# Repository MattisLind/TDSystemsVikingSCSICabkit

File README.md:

# Adapter board for Viking SCSI cards

This is an adapter board for the TD Systems line of Viking SCSI cards for DEC Qbus and Unibus.
It is an replica of the original by TD Systems.

| Component designator | Commponent | Manufacturer | Manufacturer ID |
|----------------------|------------|--------------|-----------------|
|      J1              | 50 pin shrouded header | ADAM TECH | [BHR-50-VUA](https://www.mouser.se/ProductDetail/737-BHR-50-VUA)  |
|      J2              | 50 pin shrouded header | ADAM TECH | [BHR-50-VUA](https://www.mouser.se/ProductDetail/737-BHR-50-VUA)  |
|      J3              | Male 25 pin DSUB solder to PCB | Amphenol | [L717TSBH25POL2RM5](https://www.mouser.se/ProductDetail/523-717TSBH25POL2RM5) |
|      J4              | Unpopulated |      |      |
|      D1              | Schottky Diode 2A 100V DO-41 | ST | [STPS2H100](https://www.mouser.se/ProductDetail/511-STPS2H100) |

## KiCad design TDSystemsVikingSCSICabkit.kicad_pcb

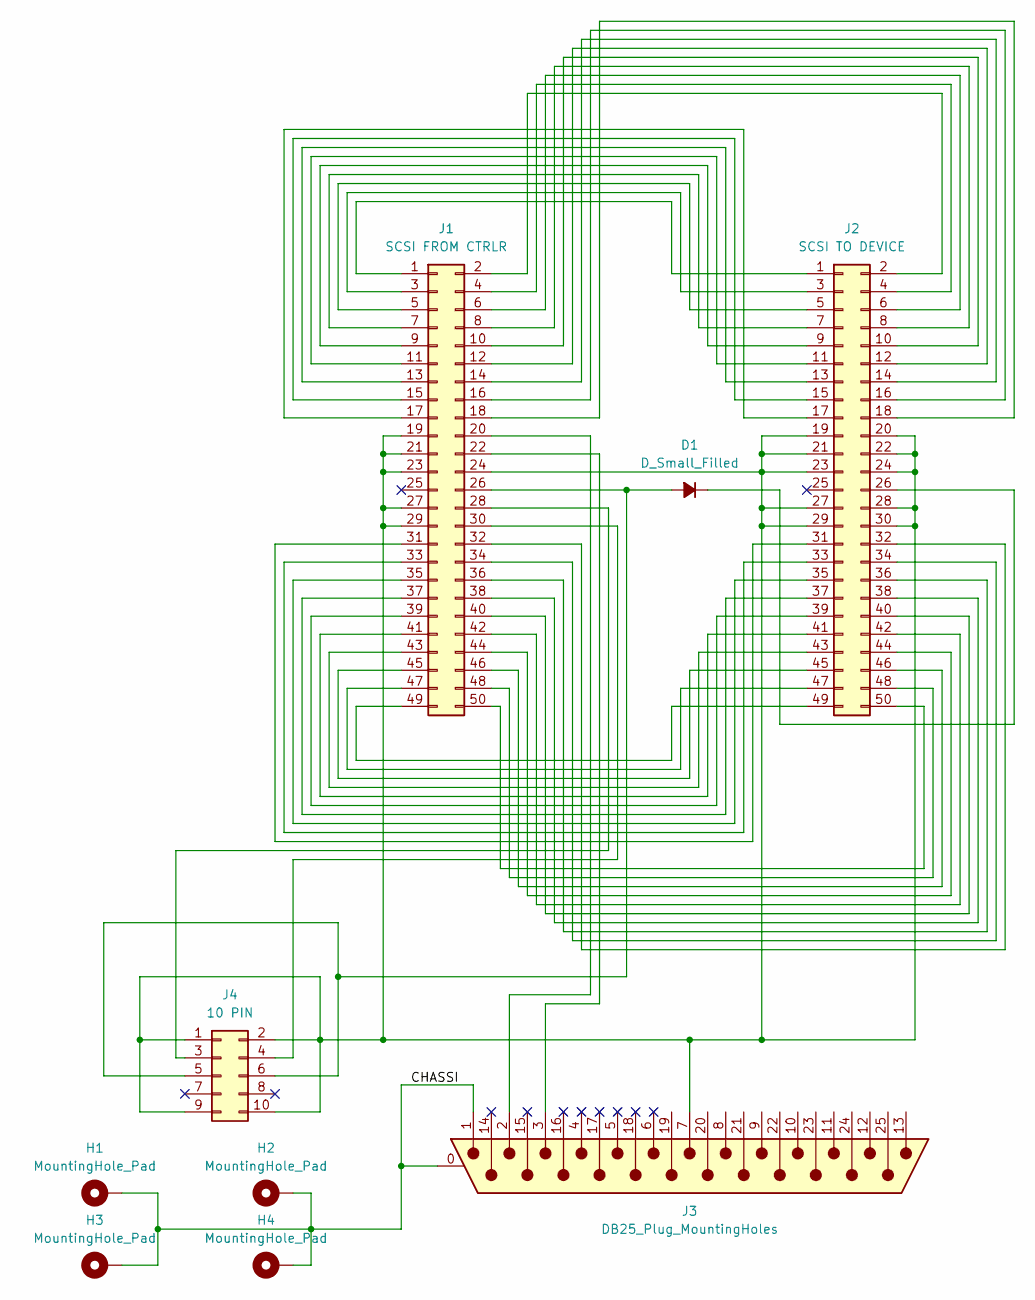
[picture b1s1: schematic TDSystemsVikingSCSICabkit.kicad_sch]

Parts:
D1: D_Small_Filled; D_DO-41_SOD81_P12.70mm_Horizontal
H1, H2, H3, H4: MountingHole_Pad; MountingHole_3.2mm_M3_Pad_Via
J1: SCSI FROM CTRLR; IDC-Header_2x25_P2.54mm_Vertical
J2: SCSI TO DEVICE; IDC-Header_2x25_P2.54mm_Vertical
J3: DB25_Plug_MountingHoles; DSUB-25_Male_Vertical_P2.77x2.84mm_MountingHoles
J4: 10 PIN; IDC-Header_2x05_P2.54mm_Vertical

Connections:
/CHASSI: H1.1, H2.1, H3.1, H4.1, J3.0 (PAD), J3.1
unnamed: D1.2 (A), J1.26, J4.5, J4.6
unnamed: D1.1 (K), J2.26
unnamed: J1.1, J2.1
unnamed: J1.2, J2.2
unnamed: J1.3, J2.3
unnamed: J1.4, J2.4
unnamed: J1.5, J2.5
unnamed: J1.6, J2.6
unnamed: J1.7, J2.7
unnamed: J1.8, J2.8
unnamed: J1.9, J2.9
unnamed: J1.10, J2.10
unnamed: J1.11, J2.11
unnamed: J1.12, J2.12
unnamed: J1.13, J2.13
unnamed: J1.14, J2.14
unnamed: J1.15, J2.15
unnamed: J1.16, J2.16
unnamed: J1.17, J2.17
unnamed: J1.18, J2.18
unnamed: J1.19, J1.21, J1.23, J1.24, J1.27, J1.29, J2.19, J2.20, J2.21, J2.22, J2.23, J2.24, J2.27, J2.28, J2.29, J2.30, J3.7, J4.1, J4.2, J4.9, J4.10
unnamed: J1.20, J3.2
unnamed: J1.22, J3.3
unnamed: J1.28, J4.3
unnamed: J1.30, J4.4
unnamed: J1.31, J2.31
unnamed: J1.32, J2.32
unnamed: J1.33, J2.33
unnamed: J1.34, J2.34
unnamed: J1.35, J2.35
unnamed: J1.36, J2.36
unnamed: J1.37, J2.37
unnamed: J1.38, J2.38
unnamed: J1.39, J2.39
unnamed: J1.40, J2.40
unnamed: J1.41, J2.41
unnamed: J1.42, J2.42
unnamed: J1.43, J2.43
unnamed: J1.44, J2.44
unnamed: J1.45, J2.45
unnamed: J1.46, J2.46
unnamed: J1.47, J2.47
unnamed: J1.48, J2.48
unnamed: J1.49, J2.49
unnamed: J1.50, J2.50

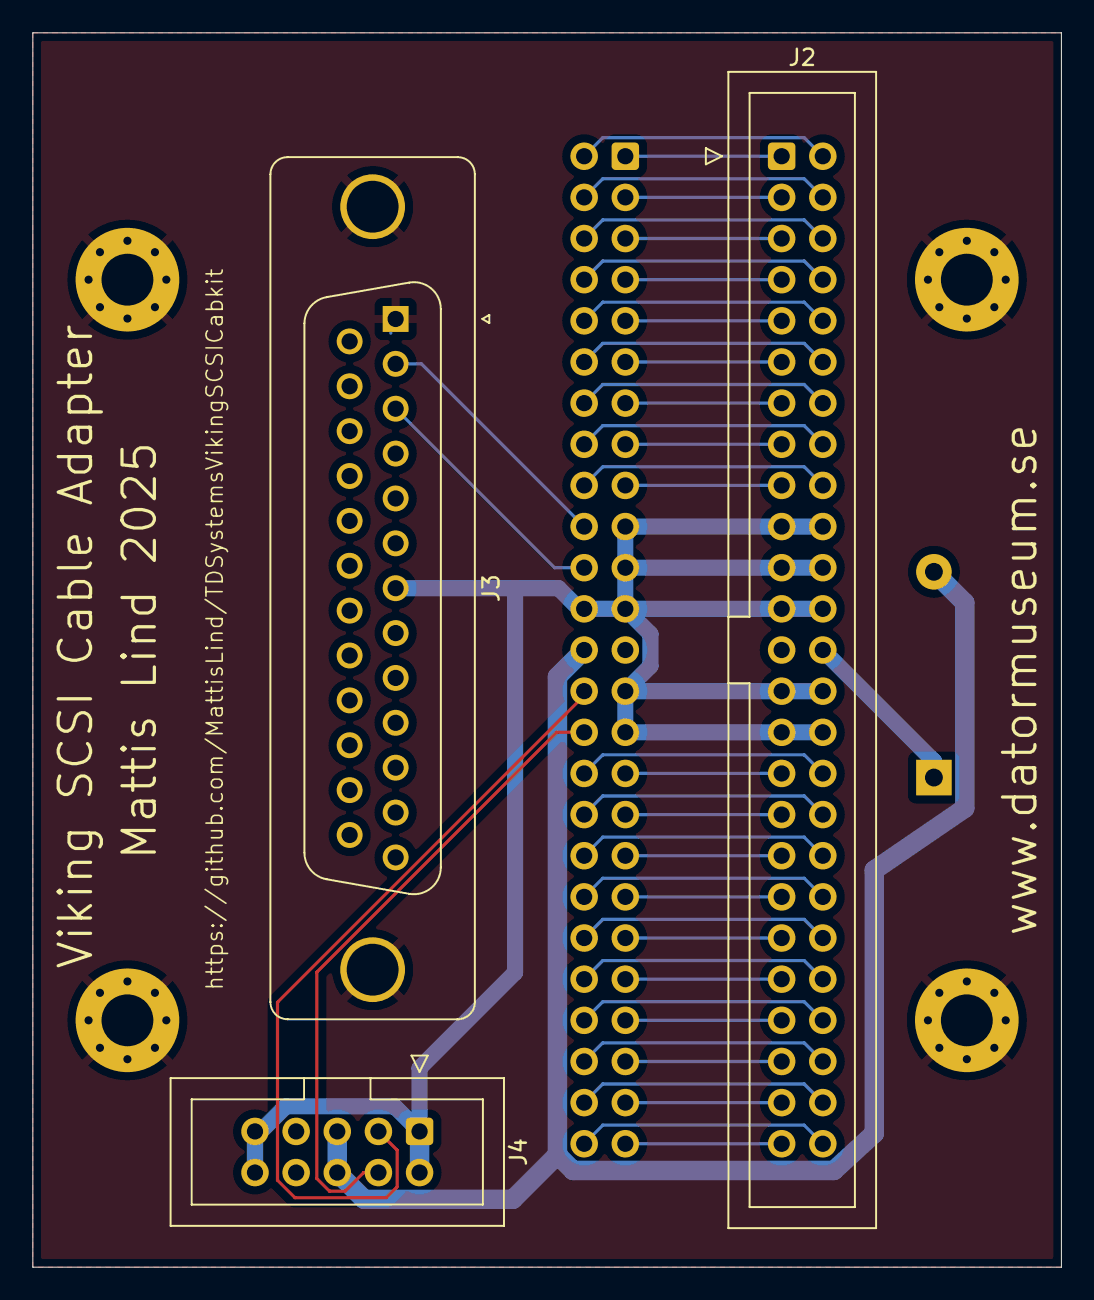
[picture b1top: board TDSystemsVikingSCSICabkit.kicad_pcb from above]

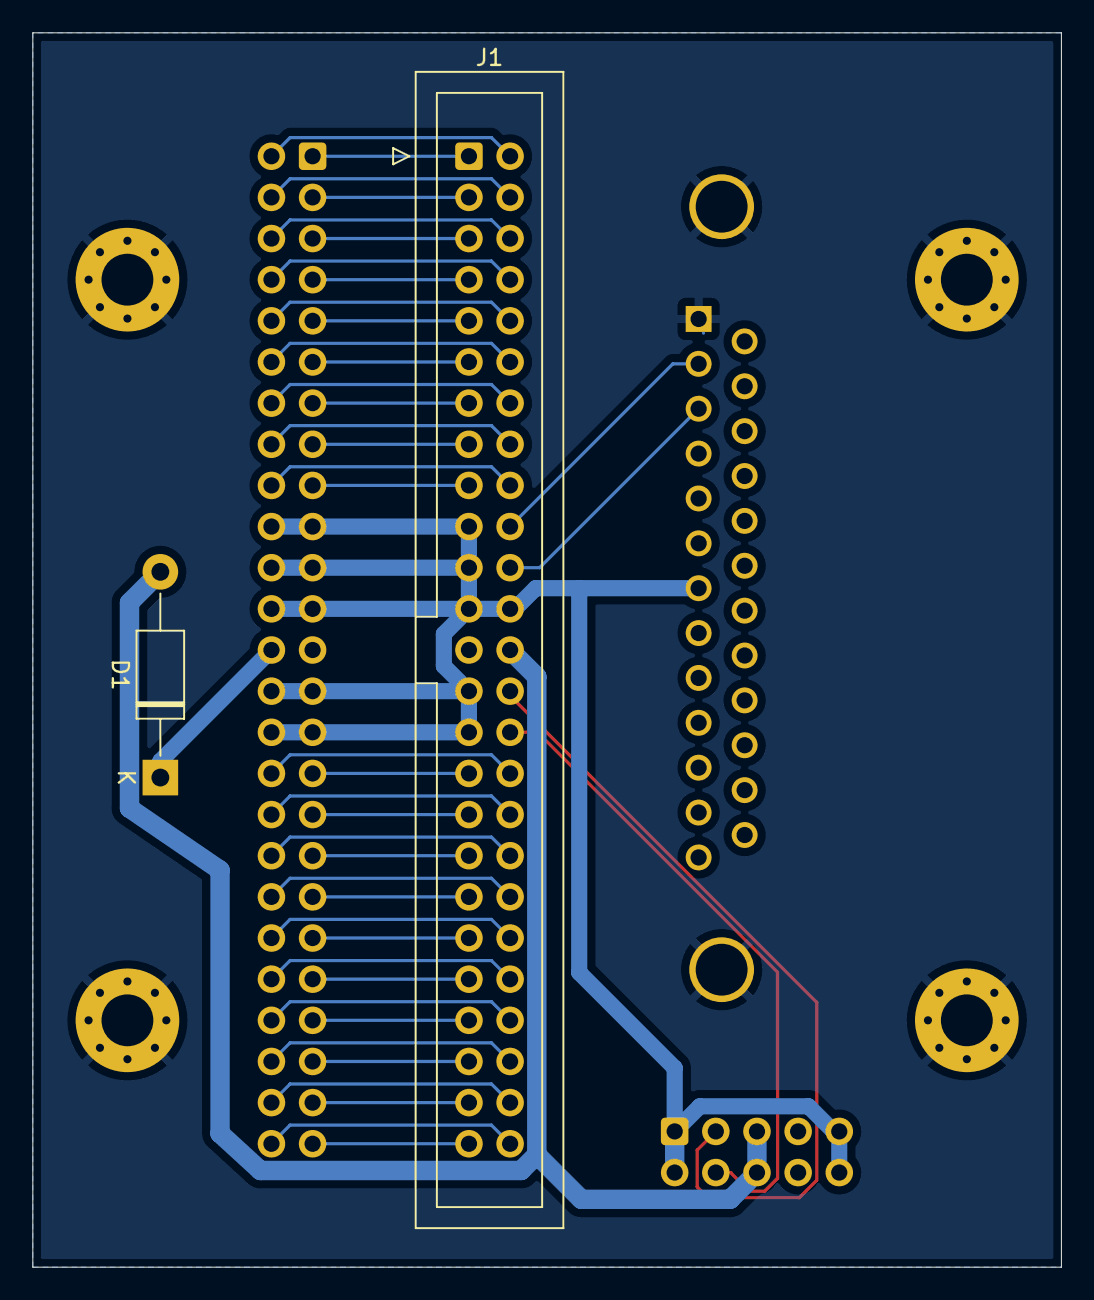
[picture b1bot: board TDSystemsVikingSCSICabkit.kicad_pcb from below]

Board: 2 copper layers, 63.5 x 76.2 mm, 9 parts (2 on the bottom side), 46 nets.

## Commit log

2025-03-10 Added pictures of board
2025-03-10 Added pictures and BOM
